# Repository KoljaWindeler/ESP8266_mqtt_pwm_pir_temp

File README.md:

# ESP8266 MQTT Repository

### Folderstructure

HA - Backup of my Homeassistant settings

JKW_MQTT_PWM_PIR_TEMP - The big deal, this is the firmware for the esp units

PCB - Some selfbuild boards based on the esp8266

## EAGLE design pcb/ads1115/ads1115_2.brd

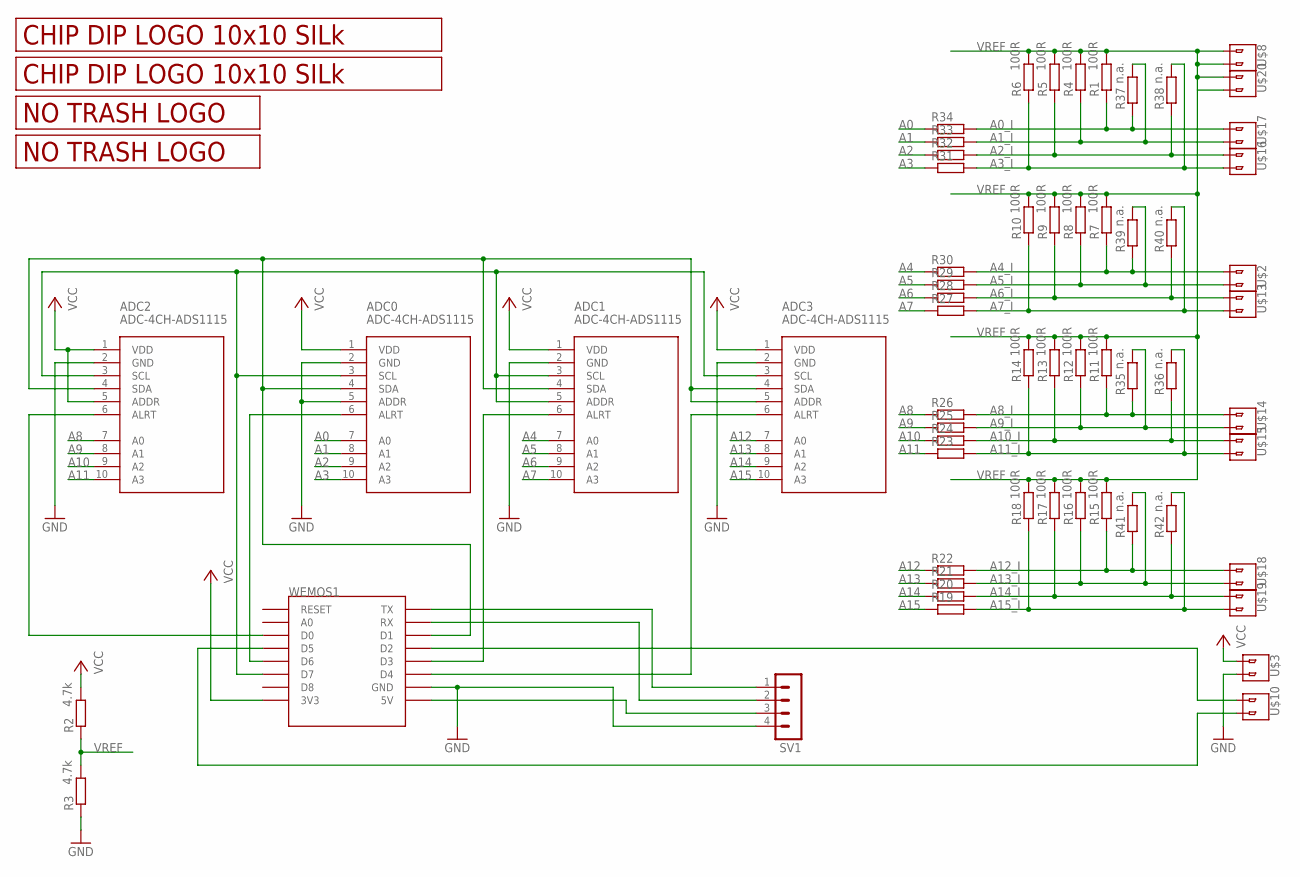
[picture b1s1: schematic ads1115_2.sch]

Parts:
ADC0, ADC1, ADC2, ADC3: ADC-4CH-ADS1115; ADC-4CH-ADS1115_NO
R1, R4, R5, R6, R7, R8, R9, R10, R11, R12, R13, R14, R15, R16, R17, R18: 100R; M0805
R2, R3: 4.7k; M0805
R19, R20, R21, R22, R23, R24, R25, R26, R27, R28, R29, R30, R31, R32, R33, R34: 1k; M0805
R35, R36, R37, R38, R39, R40, R41, R42: n.a.; M0805
SV1: MA04-1
U$1, U$11: LOGO_10X10_SILK; LOGO2_10X10_SILK
U$2, U$3, U$8, U$10, U$13, U$14, U$15, U$16, U$17, U$18, U$19, U$20: V1; 2_SCREW_PIN
U$4: LOGO_NO_TRASHNO_TRASH; LOGO_ROHS_NO_TRASH
U$9: LOGO_NO_TRASHROHS; LOGO_ROHS_SYM
WEMOS1: WEMOS-D1-MINITXT; WEMOS-D1-MINI

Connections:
A0: ADC0.7 (A0), R34.1
A0_I: R1.1, R34.2, R37.1, U$17.P$1 (1)
A1: ADC0.8 (A1), R33.1
A1_I: R4.1, R33.2, R37.2, U$17.P$2 (2)
A2: ADC0.9 (A2), R32.1
A2_I: R5.1, R32.2, R38.1, U$16.P$1 (1)
A3: ADC0.10 (A3), R31.1
A3_I: R6.1, R31.2, R38.2, U$16.P$2 (2)
A4: ADC1.7 (A0), R30.1
A4_I: R7.1, R30.2, R39.1, U$2.P$1 (1)
A5: ADC1.8 (A1), R29.1
A5_I: R8.1, R29.2, R39.2, U$2.P$2 (2)
A6: ADC1.9 (A2), R28.1
A6_I: R9.1, R28.2, R40.1, U$13.P$1 (1)
A7: ADC1.10 (A3), R27.1
A7_I: R10.1, R27.2, R40.2, U$13.P$2 (2)
A8: ADC2.7 (A0), R26.1
A8_I: R11.1, R26.2, R35.1, U$14.P$1 (1)
A9: ADC2.8 (A1), R25.1
A9_I: R12.1, R25.2, R35.2, U$14.P$2 (2)
A10: ADC2.9 (A2), R24.1
A10_I: R13.1, R24.2, R36.1, U$15.P$1 (1)
A11: ADC2.10 (A3), R23.1
A11_I: R14.1, R23.2, R36.2, U$15.P$2 (2)
A12: ADC3.7 (A0), R22.1
A12_I: R15.1, R22.2, R41.1, U$18.P$1 (1)
A13: ADC3.8 (A1), R21.1
A13_I: R16.1, R21.2, R41.2, U$18.P$2 (2)
A14: ADC3.9 (A2), R20.1
A14_I: R17.1, R20.2, R42.1, U$19.P$1 (1)
A15: ADC3.10 (A3), R19.1
A15_I: R18.1, R19.2, R42.2, U$19.P$2 (2)
GND: ADC0.2 (GND), ADC0.5 (ADDR), ADC1.2 (GND), ADC2.2 (GND), ADC3.2 (GND), R3.1, SV1.4, U$3.P$2 (2), WEMOS1.GND
unnamed: SV1.1, WEMOS1.TX
unnamed: SV1.2, WEMOS1.RX
unnamed: SV1.3, WEMOS1.5V
unnamed: ADC0.6 (ALRT), WEMOS1.D6
unnamed: U$10.P$2 (2), WEMOS1.D5
unnamed: U$10.P$1 (1), WEMOS1.D2
unnamed: ADC0.4 (SDA), ADC1.4 (SDA), ADC2.4 (SDA), ADC3.4 (SDA), ADC3.5 (ADDR), WEMOS1.D1
unnamed: ADC3.6 (ALRT), WEMOS1.D4
unnamed: ADC1.6 (ALRT), WEMOS1.D3
unnamed: ADC0.3 (SCL), ADC1.3 (SCL), ADC1.5 (ADDR), ADC2.3 (SCL), ADC3.3 (SCL), WEMOS1.D7
unnamed: ADC2.6 (ALRT), WEMOS1.D0
VCC: ADC0.1 (VDD), ADC1.1 (VDD), ADC2.1 (VDD), ADC2.5 (ADDR), ADC3.1 (VDD), R2.2, U$3.P$1 (1), WEMOS1.3V3
VREF: R1.2, R2.1, R3.2, R4.2, R5.2, R6.2, R7.2, R8.2, R9.2, R10.2, R11.2, R12.2, R13.2, R14.2, R15.2, R16.2, R17.2, R18.2, U$8.P$1 (1), U$8.P$2 (2), U$20.P$1 (1), U$20.P$2 (2)

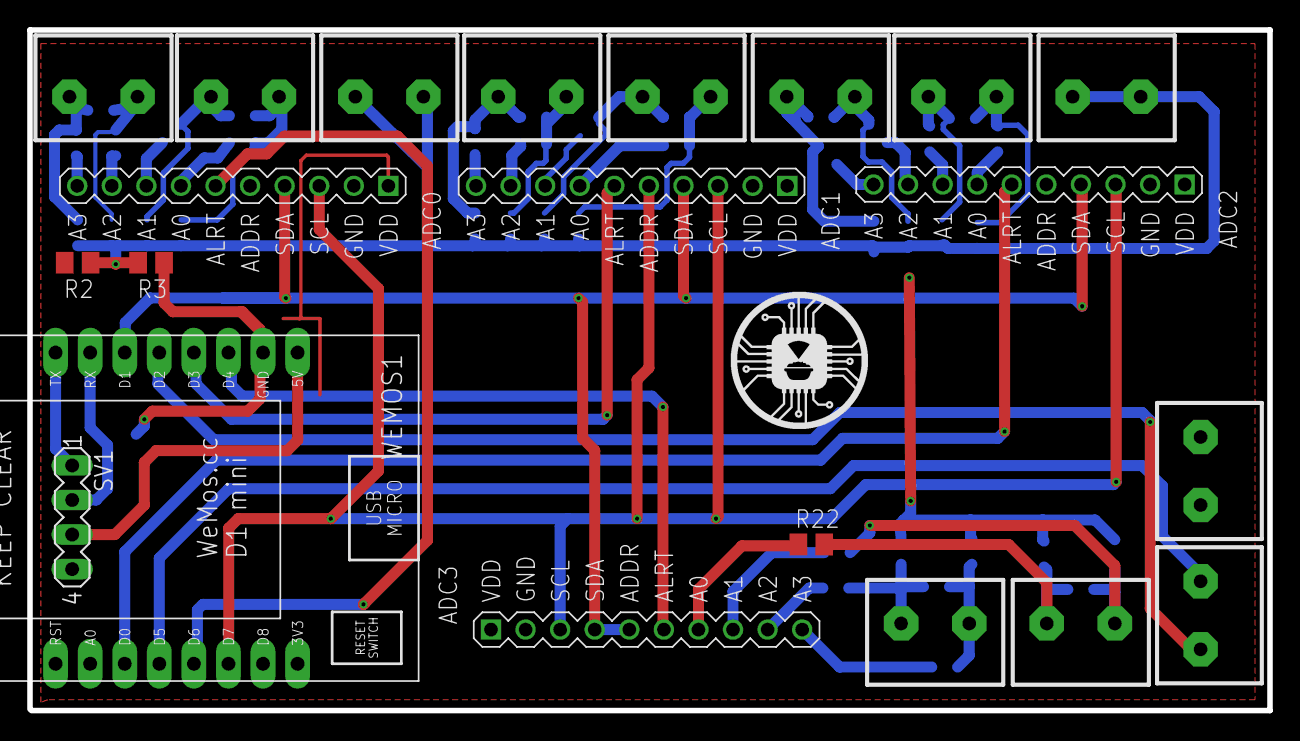
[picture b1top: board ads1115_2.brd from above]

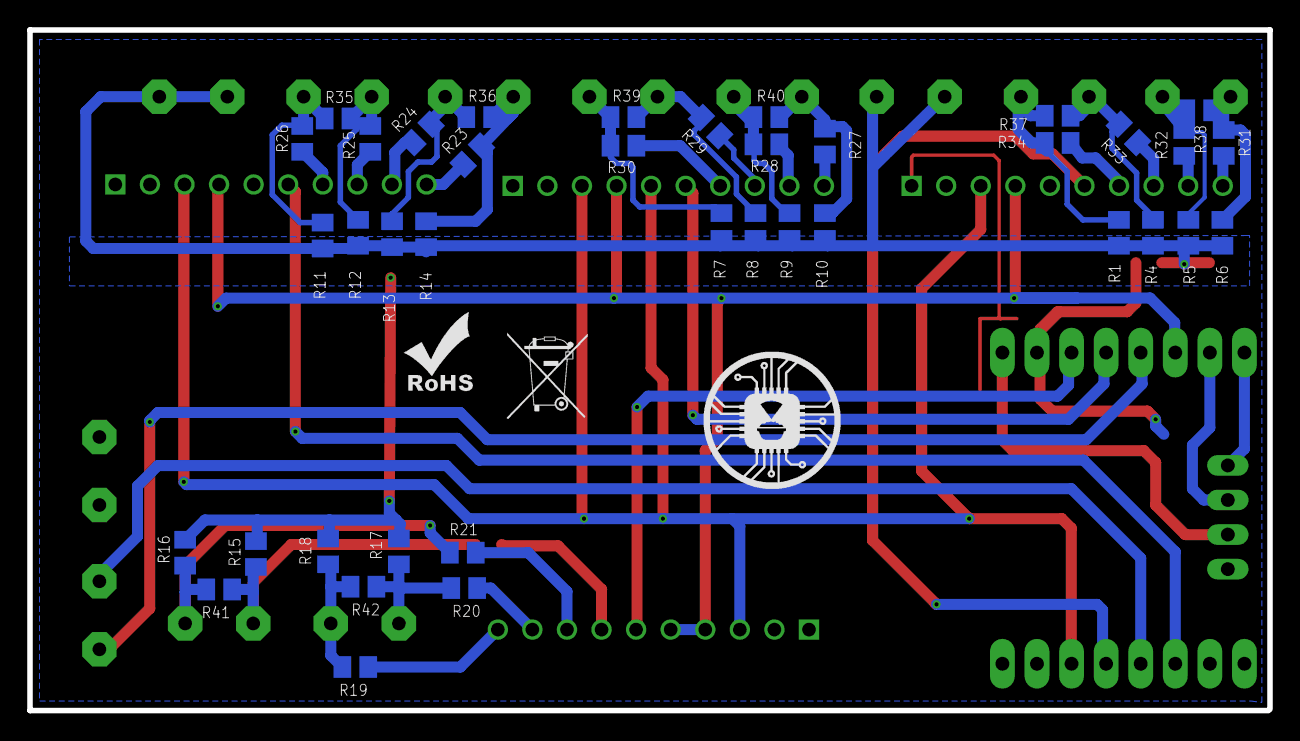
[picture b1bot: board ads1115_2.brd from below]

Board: 2 copper layers, 91.1 x 50.0 mm, 64 parts (42 on the bottom side), 46 nets.

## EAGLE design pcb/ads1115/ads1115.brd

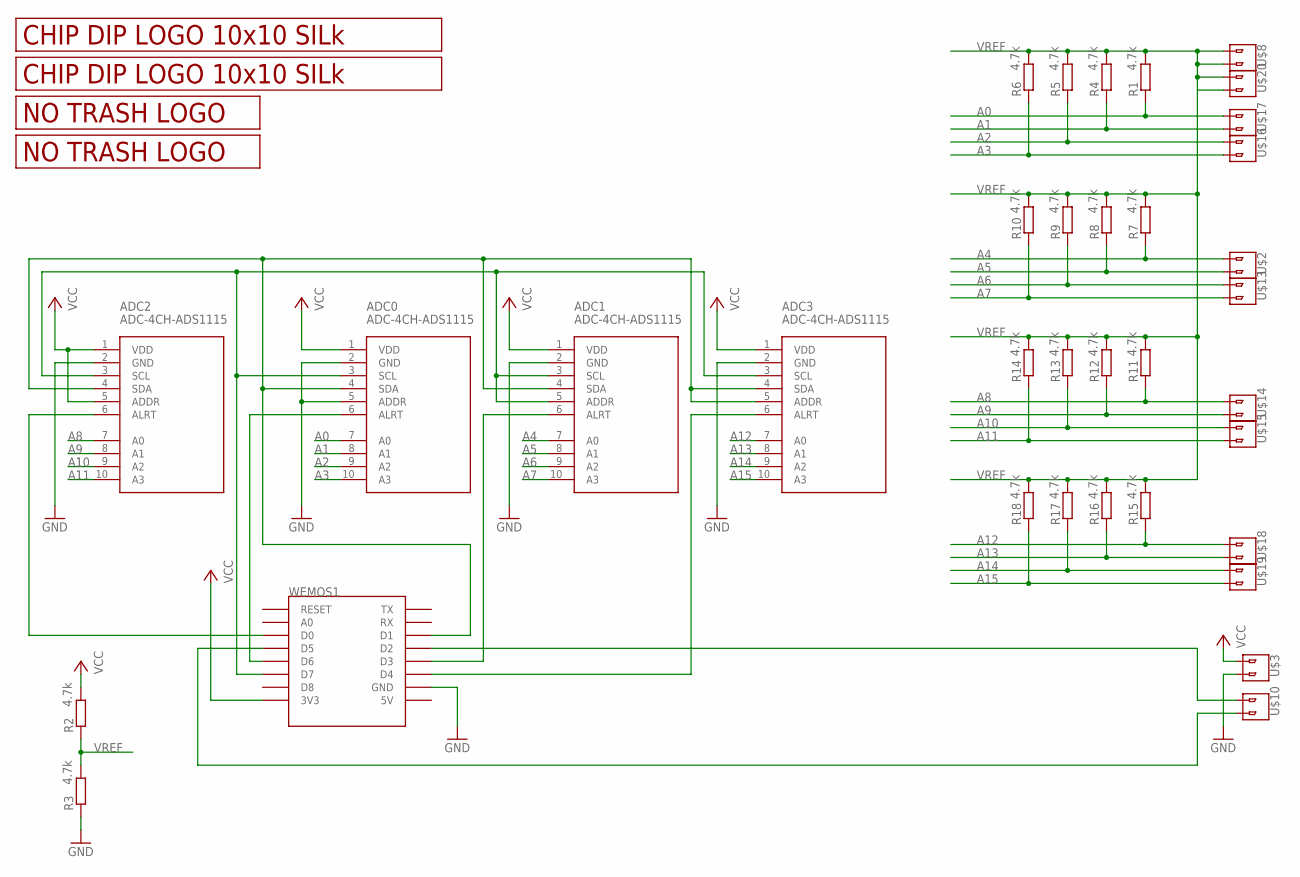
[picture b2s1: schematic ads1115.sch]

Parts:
ADC0, ADC1, ADC2, ADC3: ADC-4CH-ADS1115; ADC-4CH-ADS1115_NO
R1, R2, R3, R4, R5, R6, R7, R8, R9, R10, R11, R12, R13, R14, R15, R16, R17, R18: 4.7k; M0805
U$1, U$11: LOGO_10X10_SILK; LOGO2_10X10_SILK
U$2, U$3, U$8, U$10, U$13, U$14, U$15, U$16, U$17, U$18, U$19, U$20: V1; 2_SCREW_PIN
U$4: LOGO_NO_TRASHNO_TRASH; LOGO_ROHS_NO_TRASH
U$9: LOGO_NO_TRASHROHS; LOGO_ROHS_SYM
WEMOS1: WEMOS-D1-MINITXT; WEMOS-D1-MINI

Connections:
A0: ADC0.7 (A0), R1.1, U$17.P$1 (1)
A1: ADC0.8 (A1), R4.1, U$17.P$2 (2)
A2: ADC0.9 (A2), R5.1, U$16.P$1 (1)
A3: ADC0.10 (A3), R6.1, U$16.P$2 (2)
A4: ADC1.7 (A0), R7.1, U$2.P$1 (1)
A5: ADC1.8 (A1), R8.1, U$2.P$2 (2)
A6: ADC1.9 (A2), R9.1, U$13.P$1 (1)
A7: ADC1.10 (A3), R10.1, U$13.P$2 (2)
A8: ADC2.7 (A0), R11.1, U$14.P$1 (1)
A9: ADC2.8 (A1), R12.1, U$14.P$2 (2)
A10: ADC2.9 (A2), R13.1, U$15.P$1 (1)
A11: ADC2.10 (A3), R14.1, U$15.P$2 (2)
A12: ADC3.7 (A0), R15.1, U$18.P$1 (1)
A13: ADC3.8 (A1), R16.1, U$18.P$2 (2)
A14: ADC3.9 (A2), R17.1, U$19.P$1 (1)
A15: ADC3.10 (A3), R18.1, U$19.P$2 (2)
GND: ADC0.2 (GND), ADC0.5 (ADDR), ADC1.2 (GND), ADC2.2 (GND), ADC3.2 (GND), R3.1, U$3.P$2 (2), WEMOS1.GND
unnamed: ADC0.6 (ALRT), WEMOS1.D6
unnamed: U$10.P$2 (2), WEMOS1.D5
unnamed: U$10.P$1 (1), WEMOS1.D2
unnamed: ADC0.4 (SDA), ADC1.4 (SDA), ADC2.4 (SDA), ADC3.4 (SDA), ADC3.5 (ADDR), WEMOS1.D1
unnamed: ADC3.6 (ALRT), WEMOS1.D4
unnamed: ADC1.6 (ALRT), WEMOS1.D3
unnamed: ADC0.3 (SCL), ADC1.3 (SCL), ADC1.5 (ADDR), ADC2.3 (SCL), ADC3.3 (SCL), WEMOS1.D7
unnamed: ADC2.6 (ALRT), WEMOS1.D0
VCC: ADC0.1 (VDD), ADC1.1 (VDD), ADC2.1 (VDD), ADC2.5 (ADDR), ADC3.1 (VDD), R2.2, U$3.P$1 (1), WEMOS1.3V3
VREF: R1.2, R2.1, R3.2, R4.2, R5.2, R6.2, R7.2, R8.2, R9.2, R10.2, R11.2, R12.2, R13.2, R14.2, R15.2, R16.2, R17.2, R18.2, U$8.P$1 (1), U$8.P$2 (2), U$20.P$1 (1), U$20.P$2 (2)

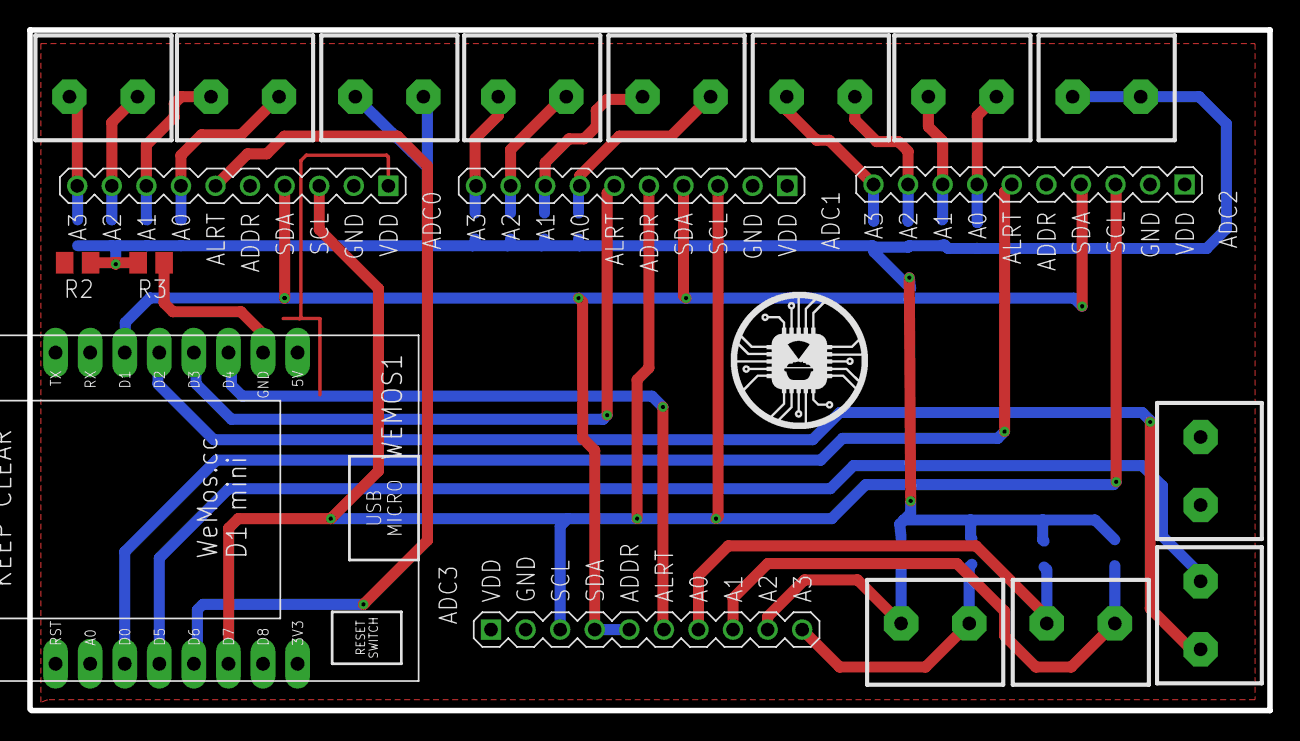
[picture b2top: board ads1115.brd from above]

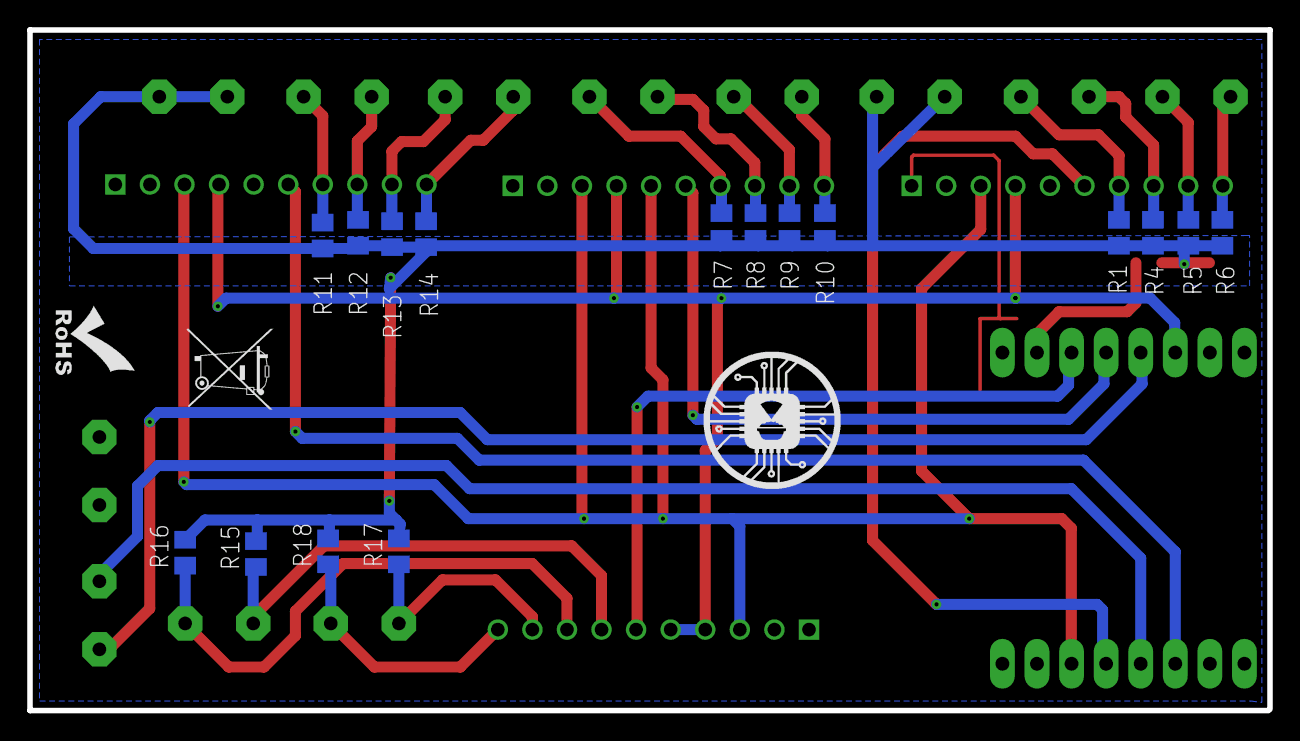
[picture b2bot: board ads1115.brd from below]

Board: 2 copper layers, 91.1 x 50.0 mm, 39 parts (19 on the bottom side), 27 nets.

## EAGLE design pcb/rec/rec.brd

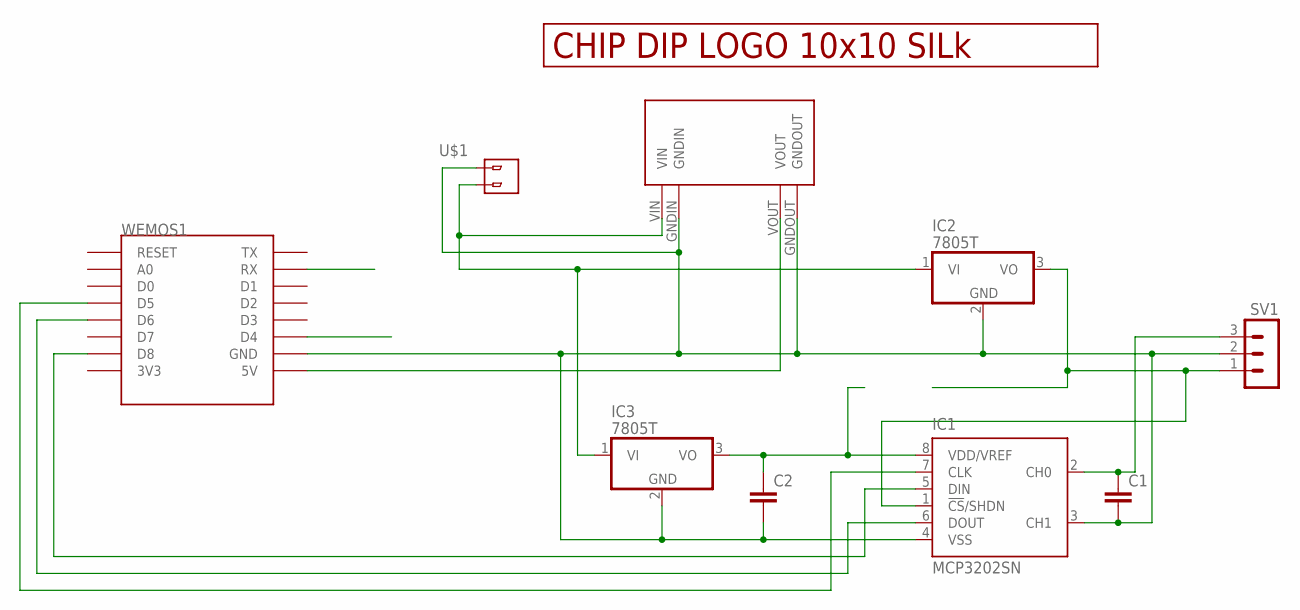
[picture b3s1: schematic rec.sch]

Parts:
C1, C2: C-EUC0805; C0805
IC1: MCP3202SN; SO-08
IC2, IC3: 7805T; TO220H
SV1: MA03-1
U$1: 2_PIN_CONNECTOR; 2_SCREW_PIN
U$2: LOGO_10X10_SILK; LOGO2_10X10_SILK
U$3: MP1584EN
WEMOS1: WEMOS-D1-MINI

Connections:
GND: C1.2, C2.2, IC1.3 (CH1), IC1.4 (VSS), IC2.2 (GND), IC3.2 (GND), SV1.2, U$1.P$1 (1), U$3.GNDIN, U$3.GNDOUT, WEMOS1.GND
unnamed: IC2.1 (VI), IC3.1 (VI), U$1.P$2 (2), U$3.VIN
unnamed: U$3.VOUT, WEMOS1.5V
unnamed: IC1.5 (DIN), WEMOS1.D8
unnamed: IC1.7 (CLK), WEMOS1.D5
unnamed: C1.1, IC1.2 (CH0), SV1.3
unnamed: IC1.1 (!CS!/SHDN), IC2.3 (VO), SV1.1
unnamed: C2.1, IC1.8 (VDD/VREF), IC3.3 (VO)
unnamed: IC1.6 (DOUT), WEMOS1.D6

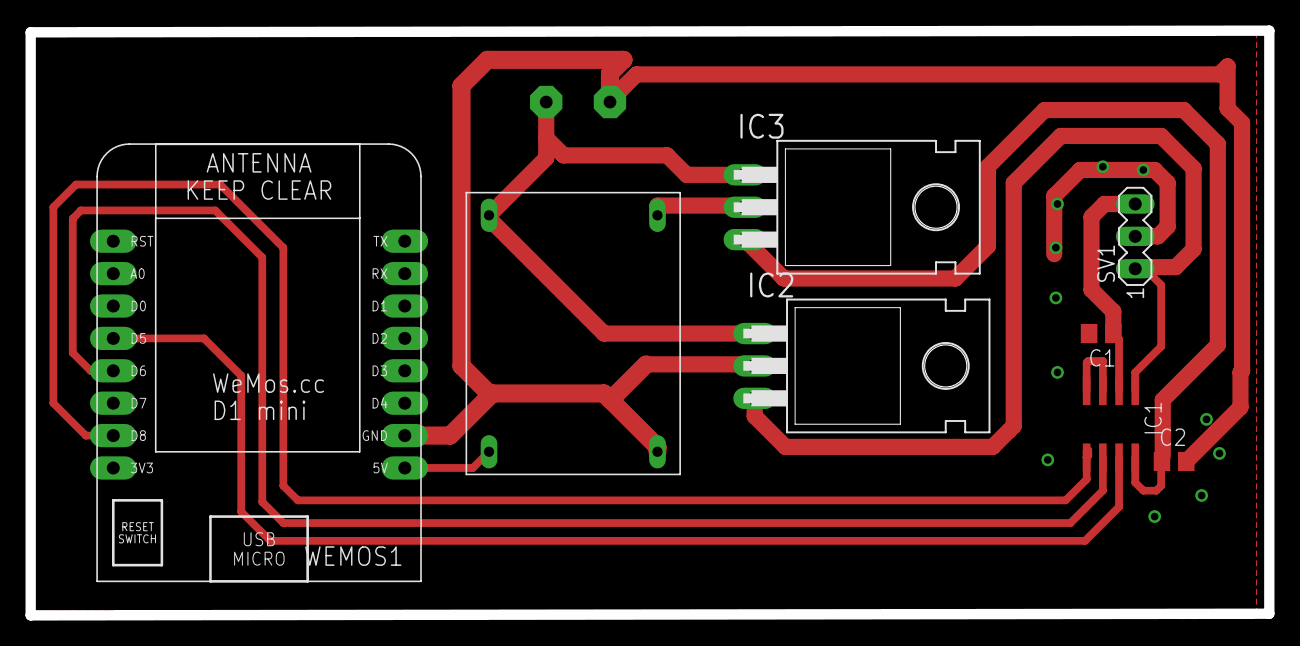
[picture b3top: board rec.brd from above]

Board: 2 copper layers, 97.1 x 45.8 mm, 10 parts (1 on the bottom side), 9 nets.

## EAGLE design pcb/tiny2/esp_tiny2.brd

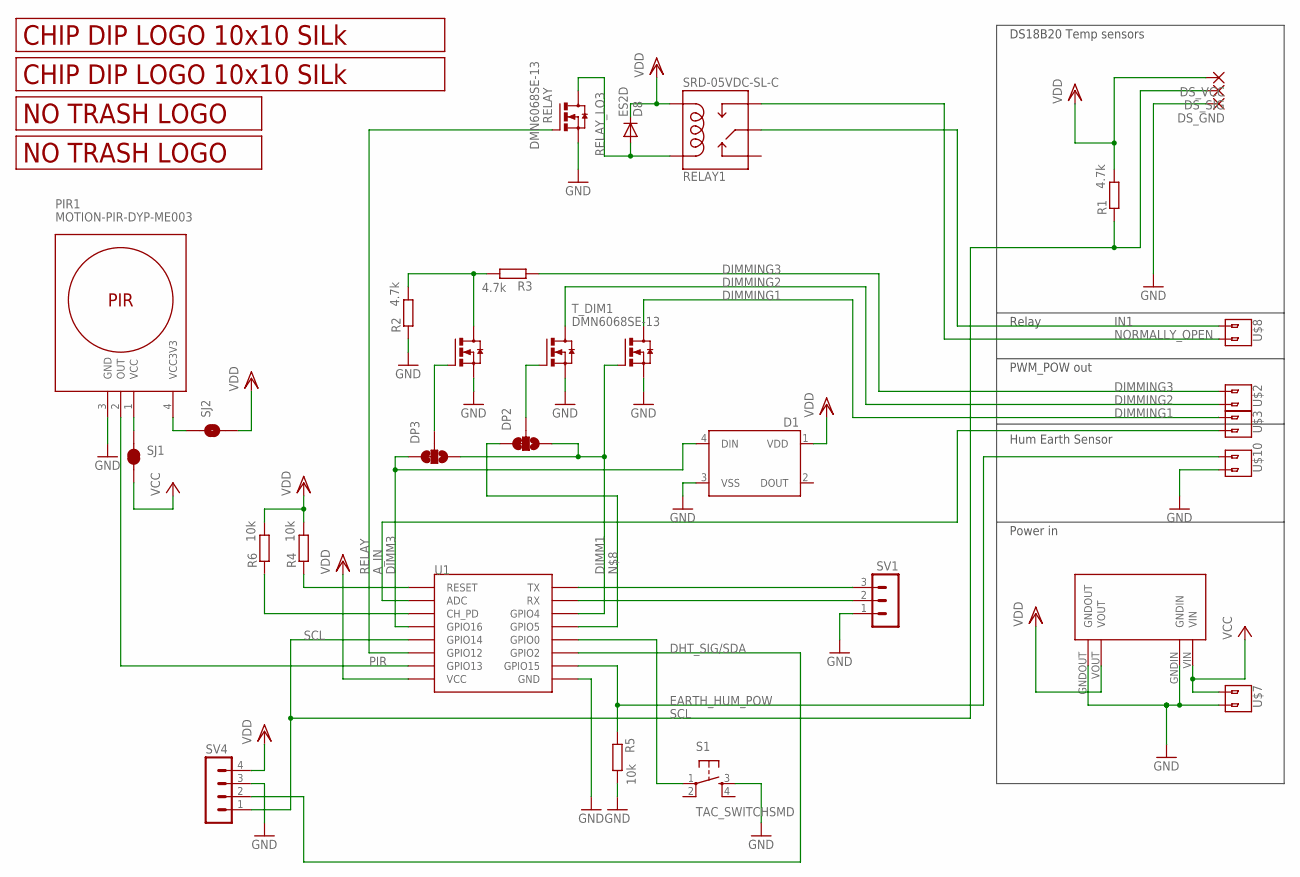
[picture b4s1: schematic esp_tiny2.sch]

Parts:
D1: WS2812B
D8: ES2D; SMB
DP2, DP3: SMD_SJ_3WAY_CLOSED
DS_GND: SMD2; SMD1,27-2,54
DS_SIG: SMD2; SMD1,27-2,54
DS_VCC: SMD2; SMD1,27-2,54
PIR1: MOTION-PIR-DYP-ME003; MOTION-PIR-DYP-ME003_FRAMELESS
R1, R2, R3: 4.7k; M0805
R4, R5, R6: 10k; M0805
RELAY: DMN6068SE-13; SOT223
RELAY1: SRD-05VDC-SL-C
S1: TAC_SWITCHSMD; TACTILE-SWITCH-SMD
SJ1: SMD_SJ_2WAY_CLOSEDCLOSED; SMD_SJ_2WAY_CLOSED
SJ2: SMD_SJ_2WAY_OPEN
SV1: MA03-1
SV4: MA04-1
T_DIM1, T_DIM2, T_DIM3: DMN6068SE-13; SOT223
U1: ESP12SMD; ESP12-SMD
U$1, U$11: LOGO_10X10_SILK; LOGO2_10X10_SILK
U$2, U$3, U$7, U$8, U$10: V1; 2_SCREW_PIN
U$4: LOGO_NO_TRASHNO_TRASH; LOGO_ROHS_NO_TRASH
U$9: LOGO_NO_TRASHROHS; LOGO_ROHS_SYM
U$12: MP1584EN

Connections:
3.3V_PIR: PIR1.4 (VCC3V3), SJ2.1
12V_PIR: PIR1.1 (VCC), SJ1.1
A_IN: U1.ADC, U$3.P$2 (2)
DHT_SIG/SDA: SV4.2, U1.GPIO2
DIMM1: DP2.3, DP3.3, T_DIM1.1 (G), U1.GPIO4
DIMM3: D1.4 (DIN), DP3.1, U1.GPIO16
DIMMING1: T_DIM1.2 (D), T_DIM1.4 (D), U$3.P$1 (1)
DIMMING2: T_DIM2.2 (D), T_DIM2.4 (D), U$2.P$2 (2)
DIMMING3: R3.1, U$2.P$1 (1)
EARTH_HUM_POW: R5.1, U1.GPIO15, U$10.P$1 (1)
GND: D1.3 (VSS), DS_GND.1, PIR1.3 (GND), R2.1, R5.2, RELAY.3 (S), S1.3, SV1.1, SV4.3, T_DIM1.3 (S), T_DIM2.3 (S), T_DIM3.3 (S), U1.GND, U$7.P$2 (2), U$10.P$2 (2), U$12.GNDIN, U$12.GNDOUT
IN1: RELAY1.SWCOMMON, U$8.P$1 (1)
unnamed: R6.1, U1.CH_PD
unnamed: R4.1, U1.RESET
unnamed: R2.2, R3.2, T_DIM3.2 (D), T_DIM3.4 (D)
unnamed: SV1.3, U1.TXD0 (TX)
unnamed: SV1.2, U1.RXD0 (RX)
unnamed: S1.1, U1.GPIO0
unnamed: DP2.1, U1.GPIO5
unnamed: DP3.2, T_DIM3.1 (G)
unnamed: DP2.2, T_DIM2.1 (G)
NORMALLY_OPEN: RELAY1.SWOPEN, U$8.P$2 (2)
PIR: PIR1.2 (OUT), U1.GPIO13
RELAY: RELAY.1 (G), U1.GPIO12
RELAY_LO3: D8.A, RELAY.2 (D), RELAY.4 (D), RELAY1.COIL1
SCL: DS_SIG.1, R1.1, SV4.1, U1.GPIO14
VCC: SJ1.3, U$7.P$1 (1), U$12.VIN
VDD: D1.1 (VDD), D8.C, DS_VCC.1, R1.2, R4.2, R6.2, RELAY1.COIL0, SJ2.3, SV4.4, U1.VCC, U$12.VOUT

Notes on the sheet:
DS18B20 Temp sensors
Relay
PWM_POW out
Hum Earth Sensor
Power in

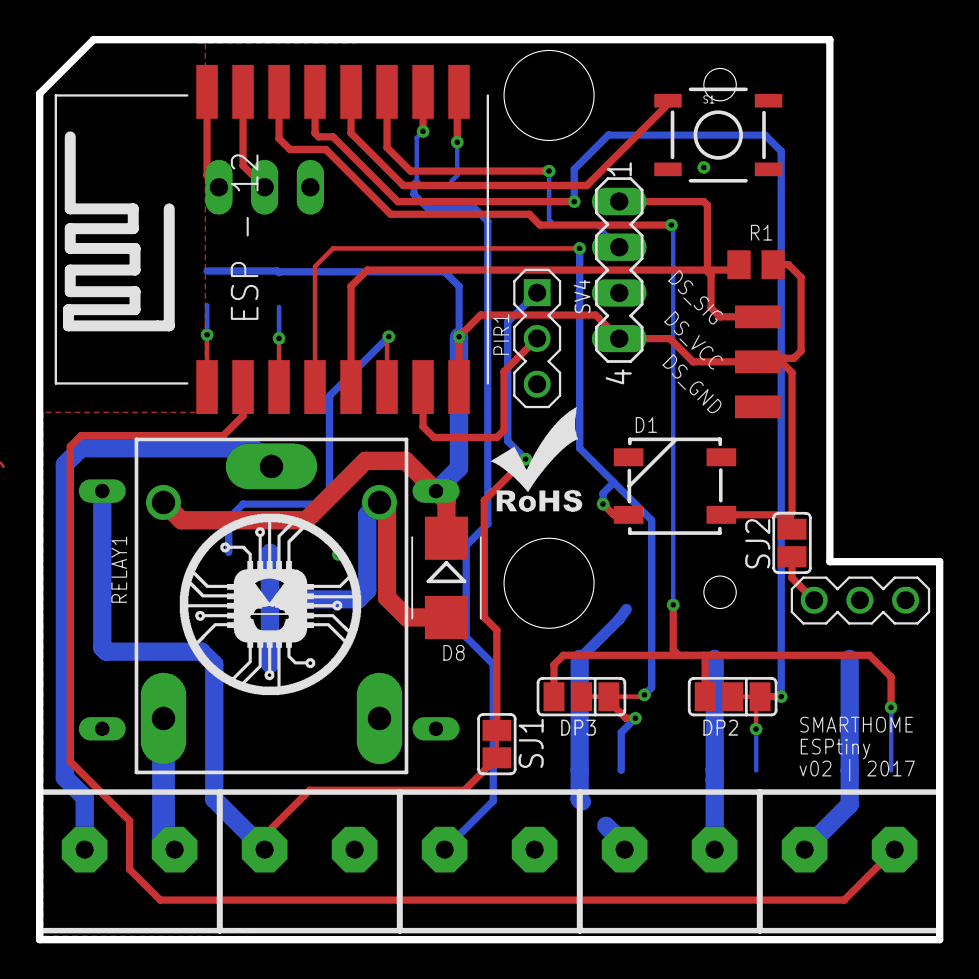
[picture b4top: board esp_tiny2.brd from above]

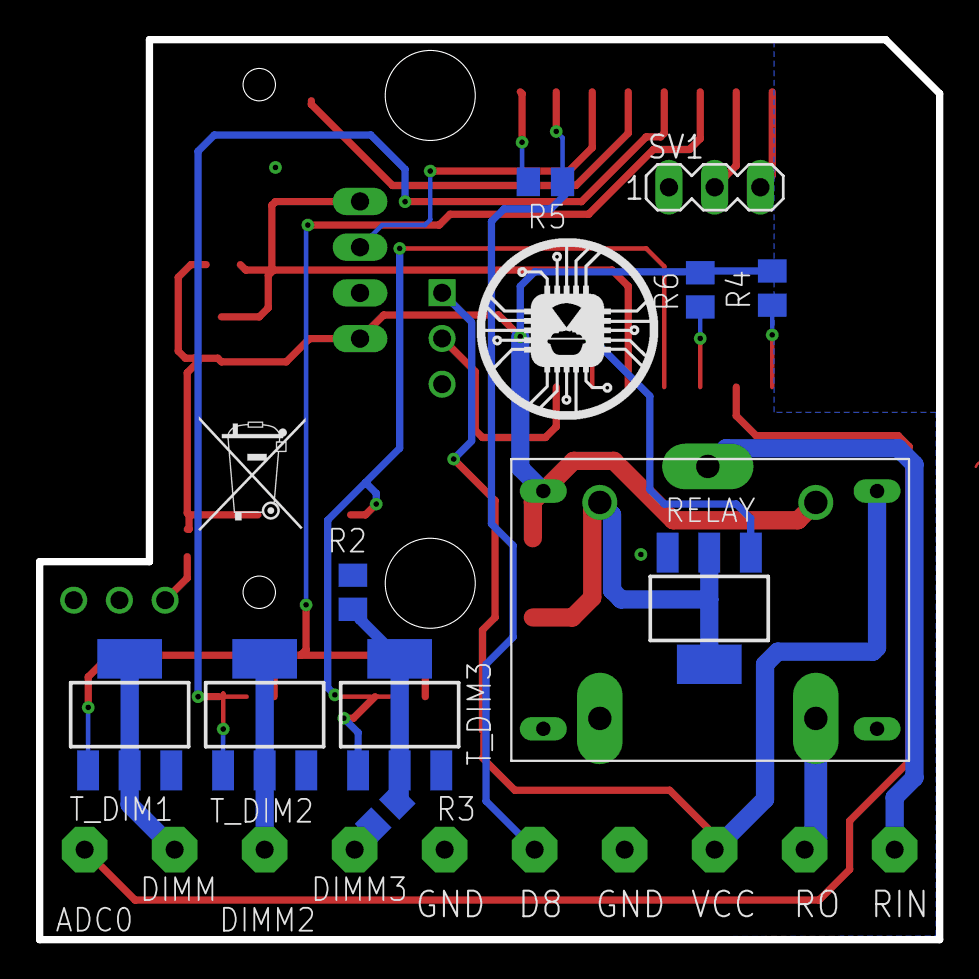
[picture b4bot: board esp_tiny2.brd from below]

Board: 2 copper layers, 50.0 x 50.0 mm, 35 parts (13 on the bottom side), 28 nets.

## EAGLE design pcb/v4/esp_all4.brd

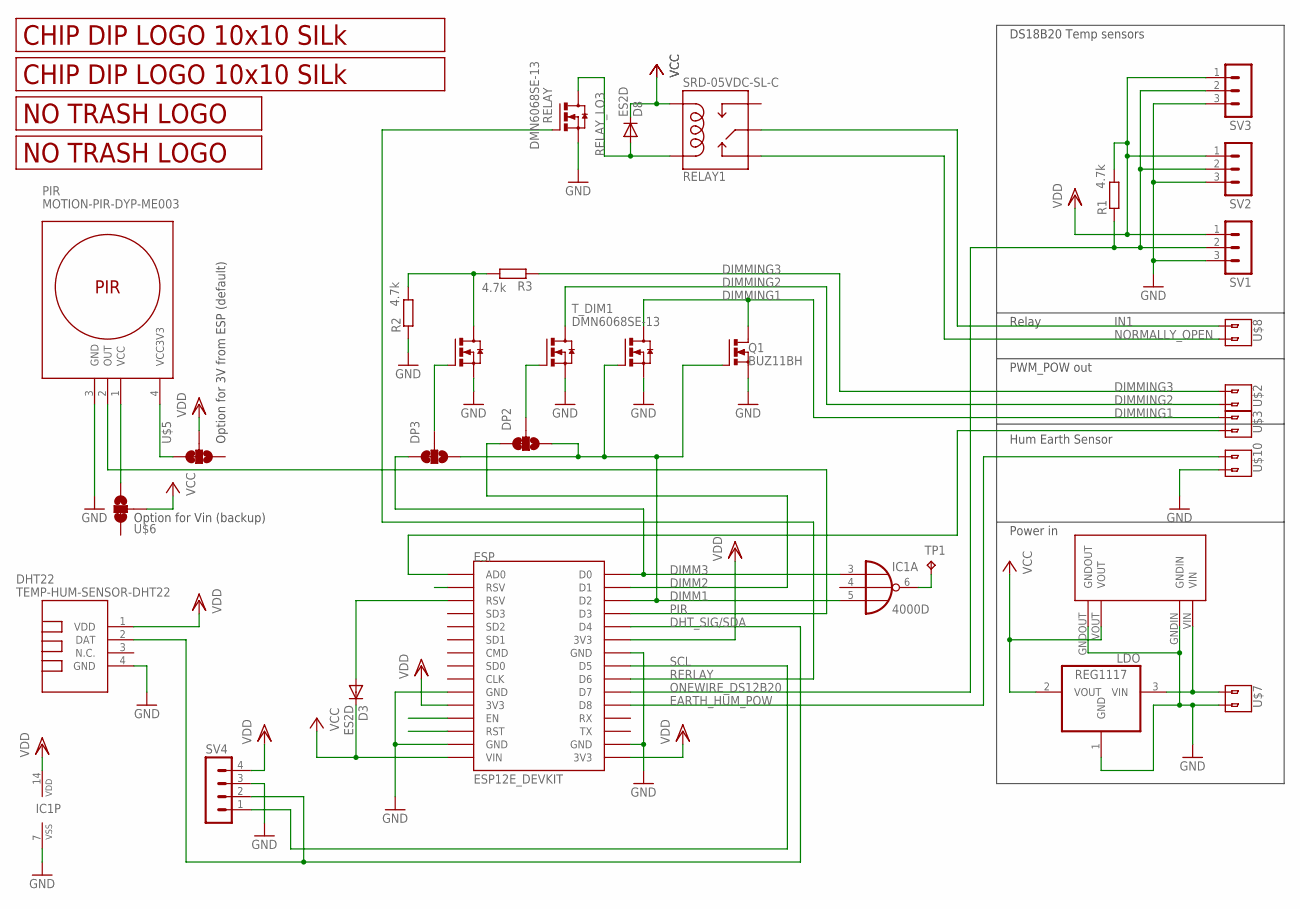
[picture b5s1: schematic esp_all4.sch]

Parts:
D3, D8: ES2D; SMB
DHT22: TEMP-HUM-SENSOR-DHT22
DP2, DP3: SMD_SJ_3WAY_CLOSED
ESP: ESP12E_DEVKIT
IC1: 4000D; SO14
LDO: REG1117; SOT223
PIR: MOTION-PIR-DYP-ME003
Q1: BUZ11BH; TO220BH
R1, R2, R3: 4.7k; M0805
RELAY: DMN6068SE-13; SOT223
RELAY1: SRD-05VDC-SL-C
SV1, SV2, SV3: MA03-1
SV4: MA04-1
TP1: TPTP20SQ; TP20SQ
T_DIM1, T_DIM2, T_DIM3: DMN6068SE-13; SOT223
U$1, U$11: LOGO_10X10_SILK; LOGO2_10X10_SILK
U$2, U$3, U$7, U$8, U$10: V1; 2_SCREW_PIN
U$4: LOGO_NO_TRASHNO_TRASH; LOGO_ROHS_NO_TRASH
U$5, U$6: SMD_SJ_3WAY_CLOSED
U$9: LOGO_NO_TRASHROHS; LOGO_ROHS_SYM
U$12: MP1584EN_FRAMELESS

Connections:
DHT_SIG/SDA: DHT22.2 (DAT), ESP.D4, ESP.D41 (D4), SV4.2
DIMM1: DP2.3, DP3.3, ESP.D2, ESP.D21 (D2), IC1.5 (I2), Q1.G, T_DIM1.1 (G)
DIMM2: DP2.1, ESP.D1, ESP.D11 (D1)
DIMM3: DP3.1, ESP.D0, ESP.D01 (D0), IC1.3 (I0)
DIMMING1: Q1.D, T_DIM1.2 (D), T_DIM1.4 (D), U$3.P$1 (1)
DIMMING2: T_DIM2.2 (D), T_DIM2.4 (D), U$2.P$2 (2)
DIMMING3: R3.1, U$2.P$1 (1)
EARTH_HUM_POW: ESP.D8, ESP.D81 (D8), U$10.P$1 (1)
GND: DHT22.4 (GND), ESP.GND@0 (GND), ESP.GND@1 (GND), ESP.GND@2 (GND), ESP.GND@3 (GND), ESP.GND@4 (GND), ESP.GND@5 (GND), ESP.GND@6 (GND), ESP.GND@7 (GND), IC1.7 (VSS), LDO.1 (GND), PIR.3 (GND), Q1.S, R2.1, RELAY.3 (S), SV1.3, SV2.3, SV3.3, SV4.3, T_DIM1.3 (S), T_DIM2.3 (S), T_DIM3.3 (S), U$7.P$2 (2), U$10.P$2 (2), U$12.GNDIN, U$12.GNDOUT
IN1: RELAY1.SWCOMMON, U$8.P$1 (1)
unnamed: ESP.AD0, ESP.AD1 (AD0), U$3.P$2 (2)
unnamed: ESP.RSV@0 (RSV), ESP.RSV@01 (RSV)
unnamed: R2.2, R3.2, T_DIM3.2 (D), T_DIM3.4 (D)
unnamed: IC1.6 (O), TP1.TP
unnamed: ESP.EN, ESP.EN1 (EN)
unnamed: ESP.RST, ESP.RST1 (RST)
unnamed: D3.A, ESP.RSV@1 (RSV), ESP.RSV@11 (RSV)
unnamed: LDO.3 (VIN), U$7.P$1 (1), U$12.VIN
unnamed: DP3.2, T_DIM3.1 (G)
unnamed: DP2.2, T_DIM2.1 (G)
unnamed: PIR.4 (VCC3V3), U$5.1
unnamed: PIR.1 (VCC), U$6.3
NORMALLY_OPEN: RELAY1.SWCLOSED (SWCLOSE), U$8.P$2 (2)
ONEWIRE_DS12B20: ESP.D7, ESP.D71 (D7), R1.1, SV1.2, SV2.2, SV3.2
PIR: ESP.D3, ESP.D31 (D3), PIR.2 (OUT)
RELAY_LO3: D8.A, RELAY.2 (D), RELAY.4 (D), RELAY1.COIL1
RERLAY: ESP.D6, ESP.D61 (D6), RELAY.1 (G)
SCL: ESP.D5, ESP.D51 (D5), SV4.1
VCC: D3.C, D8.C, ESP.VIN, ESP.VIN1 (VIN), LDO.2 (VOUT), RELAY1.COIL0, U$6.2, U$12.VOUT
VDD: DHT22.1 (VDD), ESP.3V3@0 (3V3), ESP.3V3@1 (3V3), ESP.3V3@2 (3V3), ESP.3V3@3 (3V3), ESP.3V3@4 (3V3), ESP.3V3@5 (3V3), IC1.14 (VDD), R1.2, SV1.1, SV2.1, SV3.1, SV4.4, U$5.2

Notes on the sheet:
DS18B20 Temp sensors
Relay
PWM_POW out
Hum Earth Sensor
Power in
Option for 3V from ESP (default)
Option for Vin (backup)

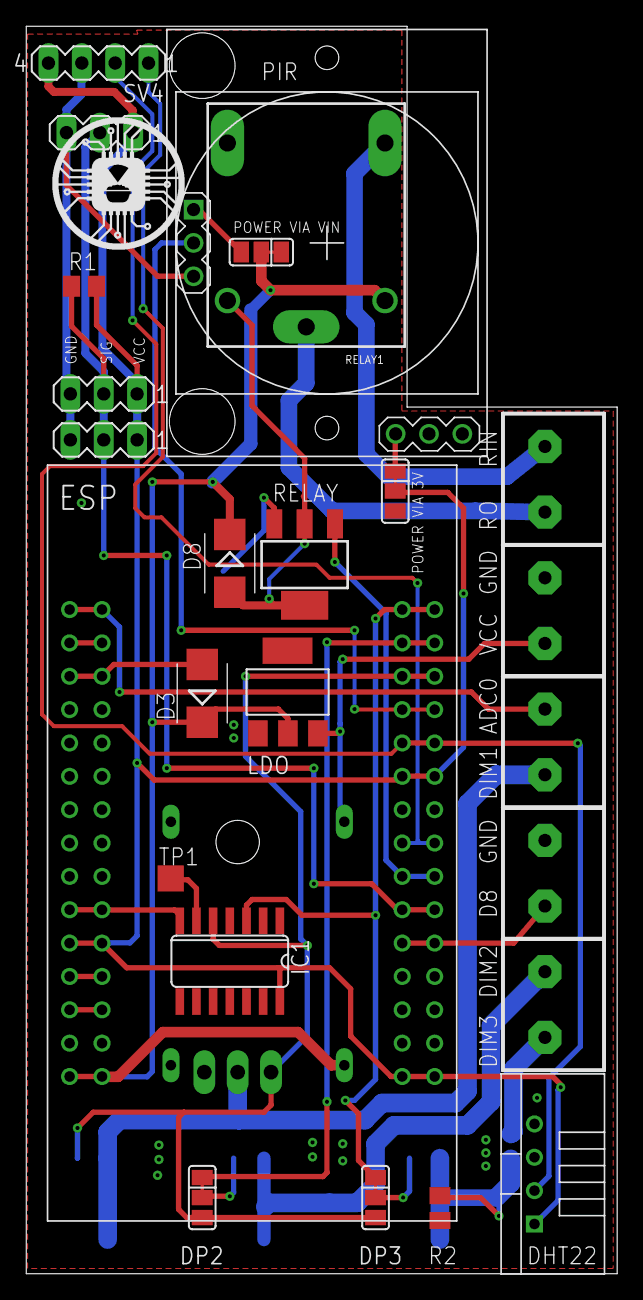
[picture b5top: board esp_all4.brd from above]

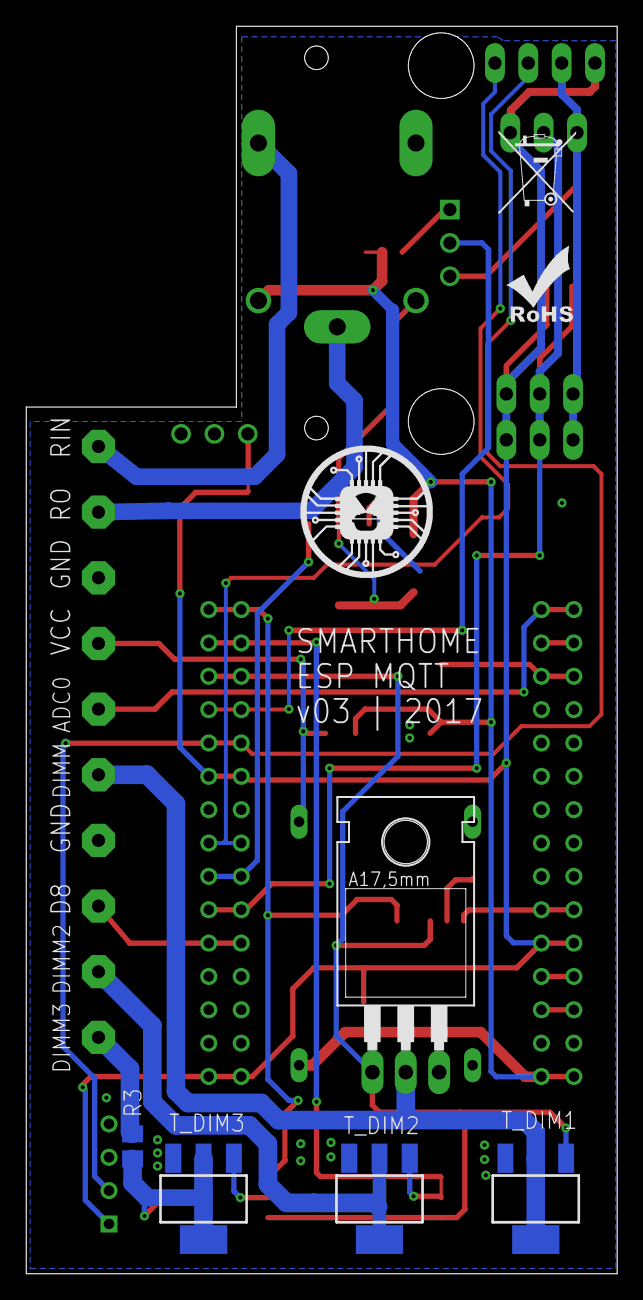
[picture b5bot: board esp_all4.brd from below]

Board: 2 copper layers, 45.0 x 95.0 mm, 35 parts (9 on the bottom side), 30 nets.

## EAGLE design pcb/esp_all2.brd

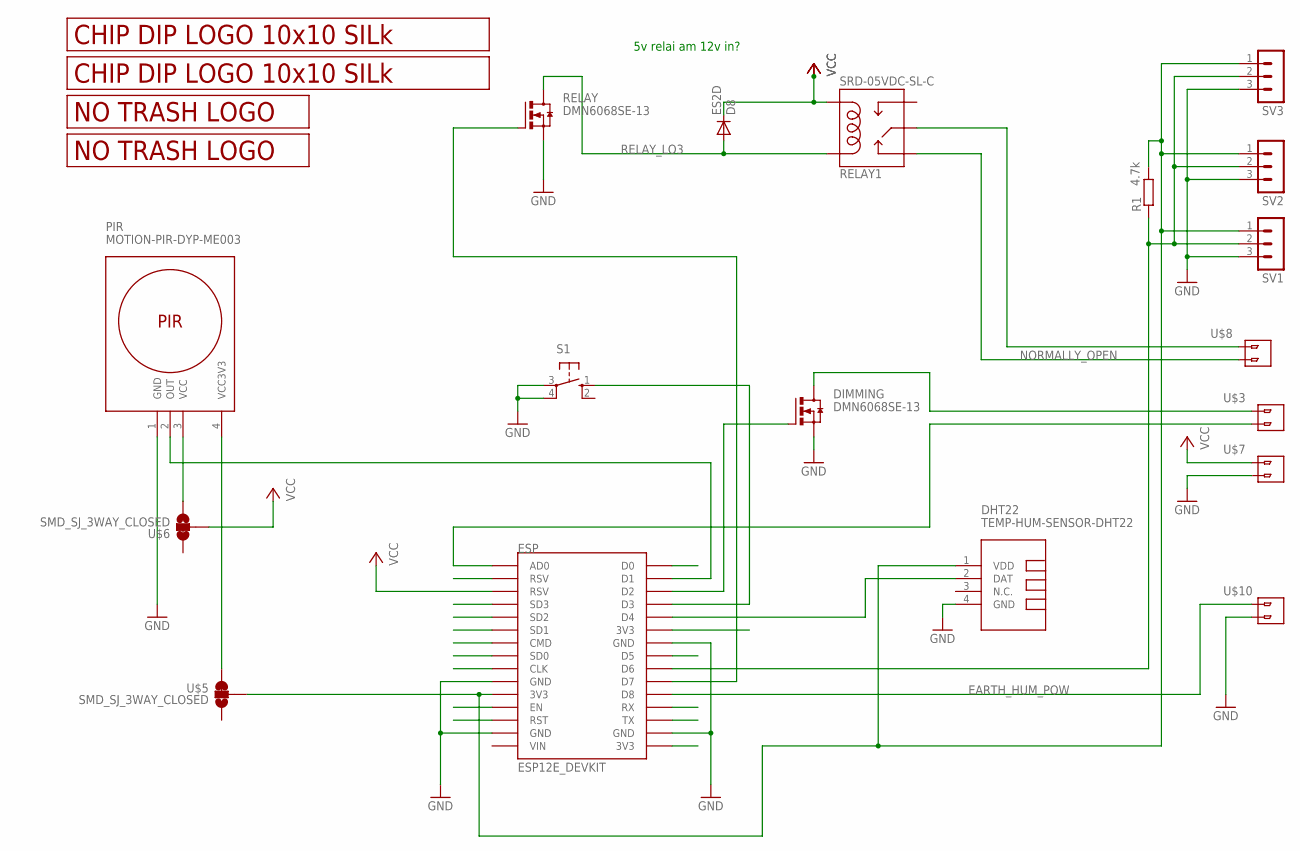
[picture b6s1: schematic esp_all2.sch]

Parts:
D8: ES2D; SMB
DHT22: TEMP-HUM-SENSOR-DHT22
DIMMING: DMN6068SE-13; SOT223
ESP: ESP12E_DEVKIT
PIR: MOTION-PIR-DYP-ME003
R1: 4.7k; M0805
RELAY: DMN6068SE-13; SOT223
RELAY1: SRD-05VDC-SL-C
S1: 40/XX; B3F/40XX
SV1, SV2, SV3: MA03-1
U$1, U$11: LOGO_10X10_SILK; LOGO2_10X10_SILK
U$3, U$7, U$8, U$10: V1; 2_SCREW_PIN
U$4: LOGO_NO_TRASHNO_TRASH; LOGO_ROHS_NO_TRASH
U$5, U$6: SMD_SJ_3WAY_CLOSED
U$9: LOGO_NO_TRASHROHS; LOGO_ROHS_SYM

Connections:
EARTH_HUM_POW: ESP.D8, ESP.D81 (D8), U$10.P$1 (1)
GND: DHT22.4 (GND), DIMMING.3 (S), ESP.GND@0 (GND), ESP.GND@1 (GND), ESP.GND@2 (GND), ESP.GND@3 (GND), ESP.GND@4 (GND), ESP.GND@5 (GND), ESP.GND@6 (GND), ESP.GND@7 (GND), PIR.1 (GND), RELAY.3 (S), S1.3, S1.4 (P1), SV1.3, SV2.3, SV3.3, U$7.P$2 (2), U$10.P$2 (2)
IN1: RELAY1.SWCOMMON, U$8.P$1 (1)
unnamed: ESP.AD0, ESP.AD1 (AD0), U$3.P$2 (2)
unnamed: ESP.RSV@0 (RSV), ESP.RSV@01 (RSV)
unnamed: ESP.SD3, ESP.SD32 (SD3)
unnamed: ESP.SD2, ESP.SD22 (SD2)
unnamed: ESP.SD1, ESP.SD12 (SD1)
unnamed: ESP.CMD, ESP.CMD1 (CMD)
unnamed: ESP.SD0, ESP.SD01 (SD0)
unnamed: ESP.CLK, ESP.CLK1 (CLK)
unnamed: ESP.D7, ESP.D71 (D7), RELAY.1 (G)
unnamed: ESP.EN, ESP.EN1 (EN)
unnamed: ESP.RST, ESP.RST1 (RST)
unnamed: ESP.D6, ESP.D61 (D6), R1.1, SV1.2, SV2.2, SV3.2
unnamed: DIMMING.2 (D), DIMMING.4 (D), U$3.P$1 (1)
unnamed: ESP.TX, ESP.TX1 (TX)
unnamed: ESP.RX, ESP.RX1 (RX)
unnamed: ESP.D5, ESP.D51 (D5)
unnamed: PIR.4 (VCC3V3), U$5.1
unnamed: DHT22.1 (VDD), ESP.3V3@0 (3V3), ESP.3V3@3 (3V3), ESP.3V3@4 (3V3), ESP.3V3@5 (3V3), R1.2, SV1.1, SV2.1, SV3.1, U$5.2
unnamed: DHT22.2 (DAT), ESP.D4, ESP.D41 (D4)
unnamed: ESP.D3, ESP.D31 (D3), S1.1 (S)
unnamed: DIMMING.1 (G), ESP.D2, ESP.D21 (D2)
unnamed: ESP.D1, ESP.D11 (D1), PIR.2 (OUT)
unnamed: ESP.D0, ESP.D01 (D0)
unnamed: PIR.3 (VCC), U$6.3
NORMALLY_OPEN: RELAY1.SWCLOSED (SWCLOSE), U$8.P$2 (2)
RELAY_LO3: D8.A, RELAY.2 (D), RELAY.4 (D), RELAY1.COIL1
VCC: D8.C, ESP.RSV@1 (RSV), ESP.RSV@11 (RSV), RELAY1.COIL0, U$6.2, U$7.P$1 (1)

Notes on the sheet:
5v relai am 12v in?

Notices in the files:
parts and their libraries:
JKW_CHIP: License : http://creativecommons.org/licenses/by-sa/3.0
(Creative Commons 3.0)
diy-modules: Released under the Creative Commons Attribution 4.0 International License: http://creativecommons.org/licenses/by/4.0
